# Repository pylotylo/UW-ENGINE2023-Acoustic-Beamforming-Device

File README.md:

# UW-ENGINE2023-Acoustic-Beamforming-Device
This is a repository for the UW ENGINE 2023 Acoustic Beamforming Device team. Here we can share drafts of our Kicad files, and any other code related to the project.

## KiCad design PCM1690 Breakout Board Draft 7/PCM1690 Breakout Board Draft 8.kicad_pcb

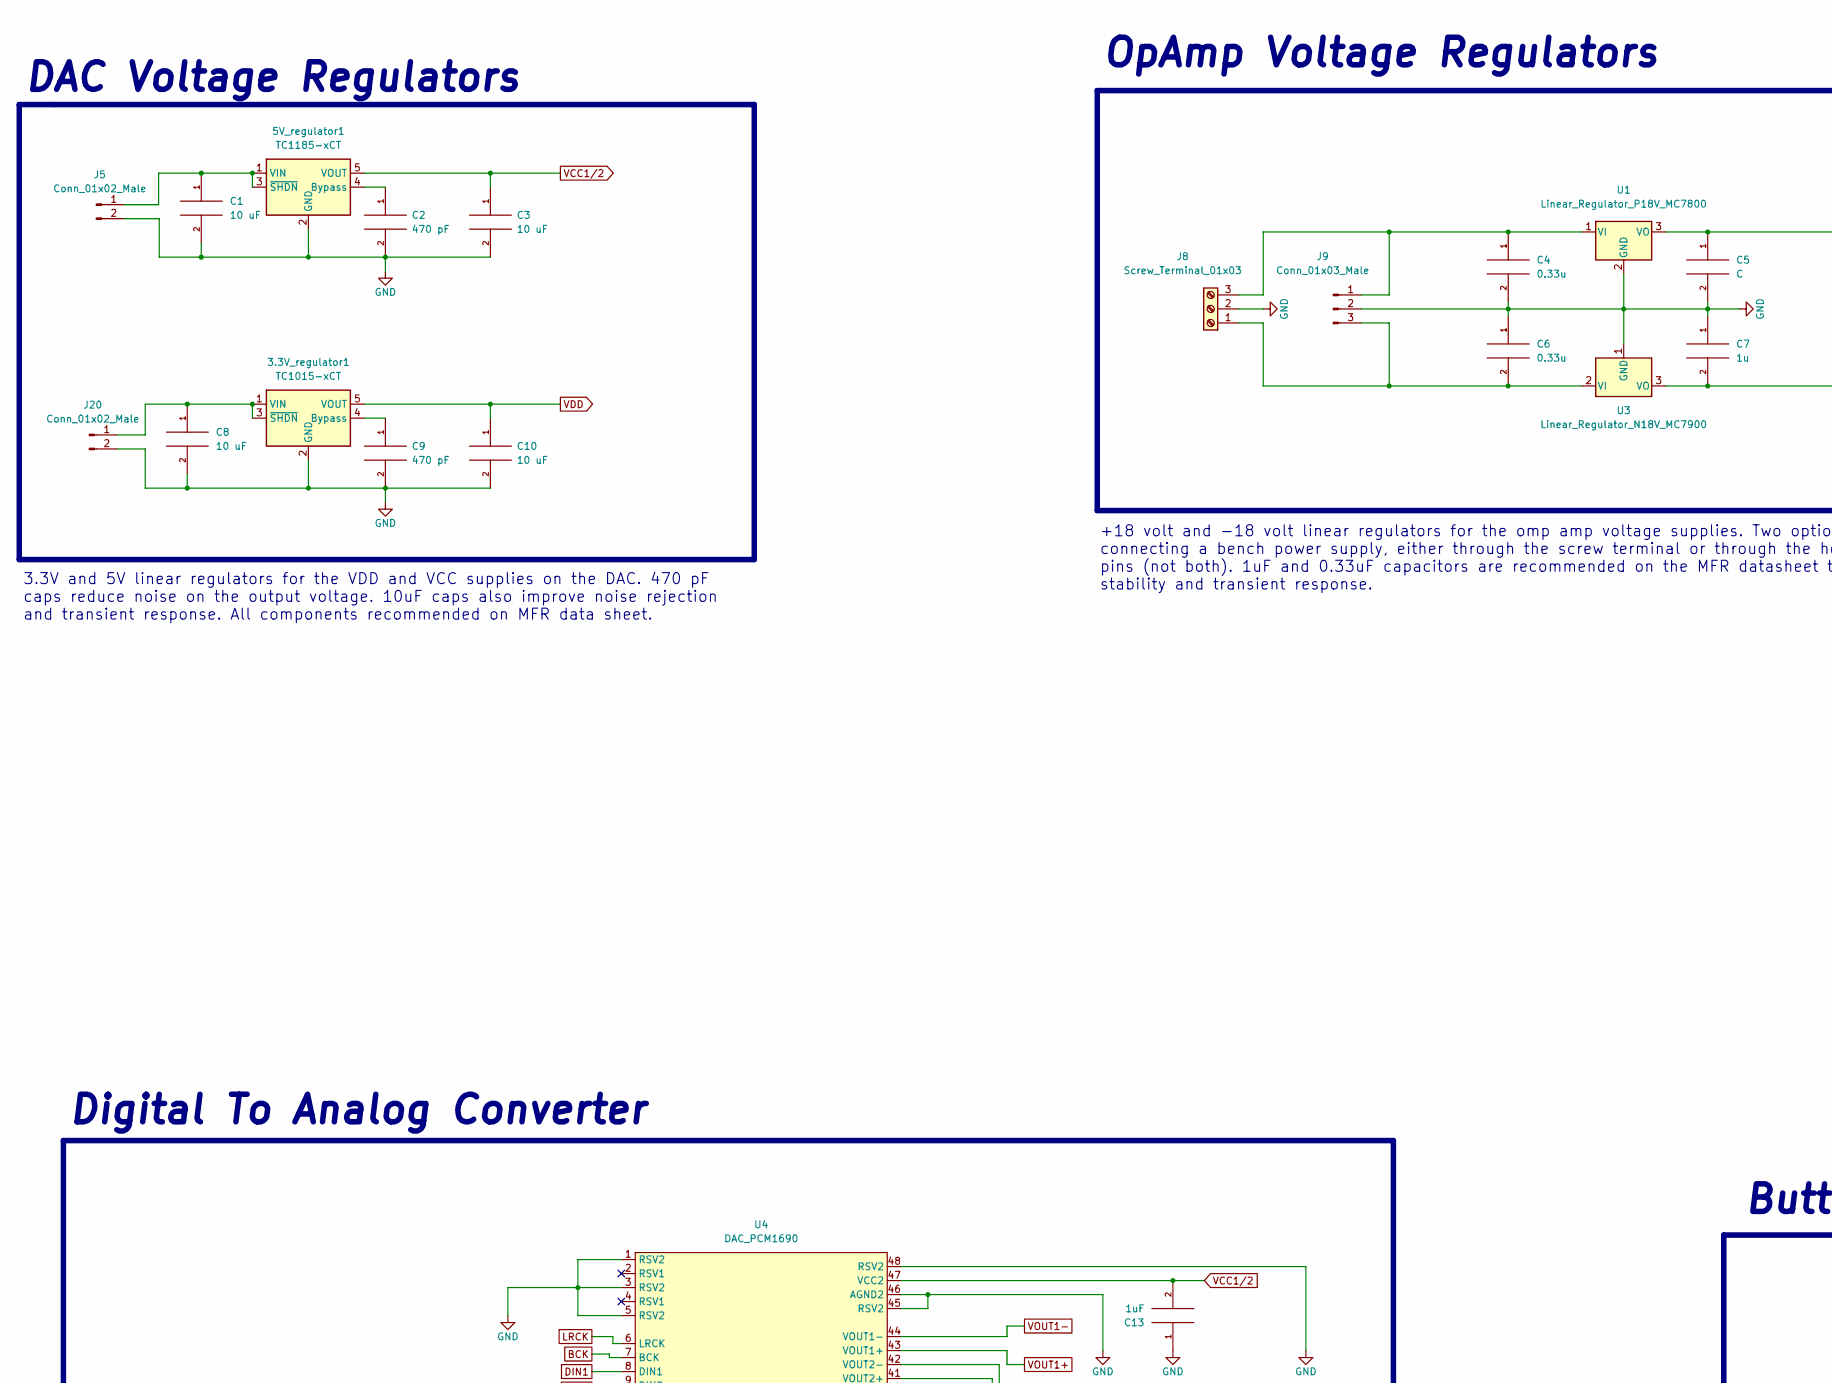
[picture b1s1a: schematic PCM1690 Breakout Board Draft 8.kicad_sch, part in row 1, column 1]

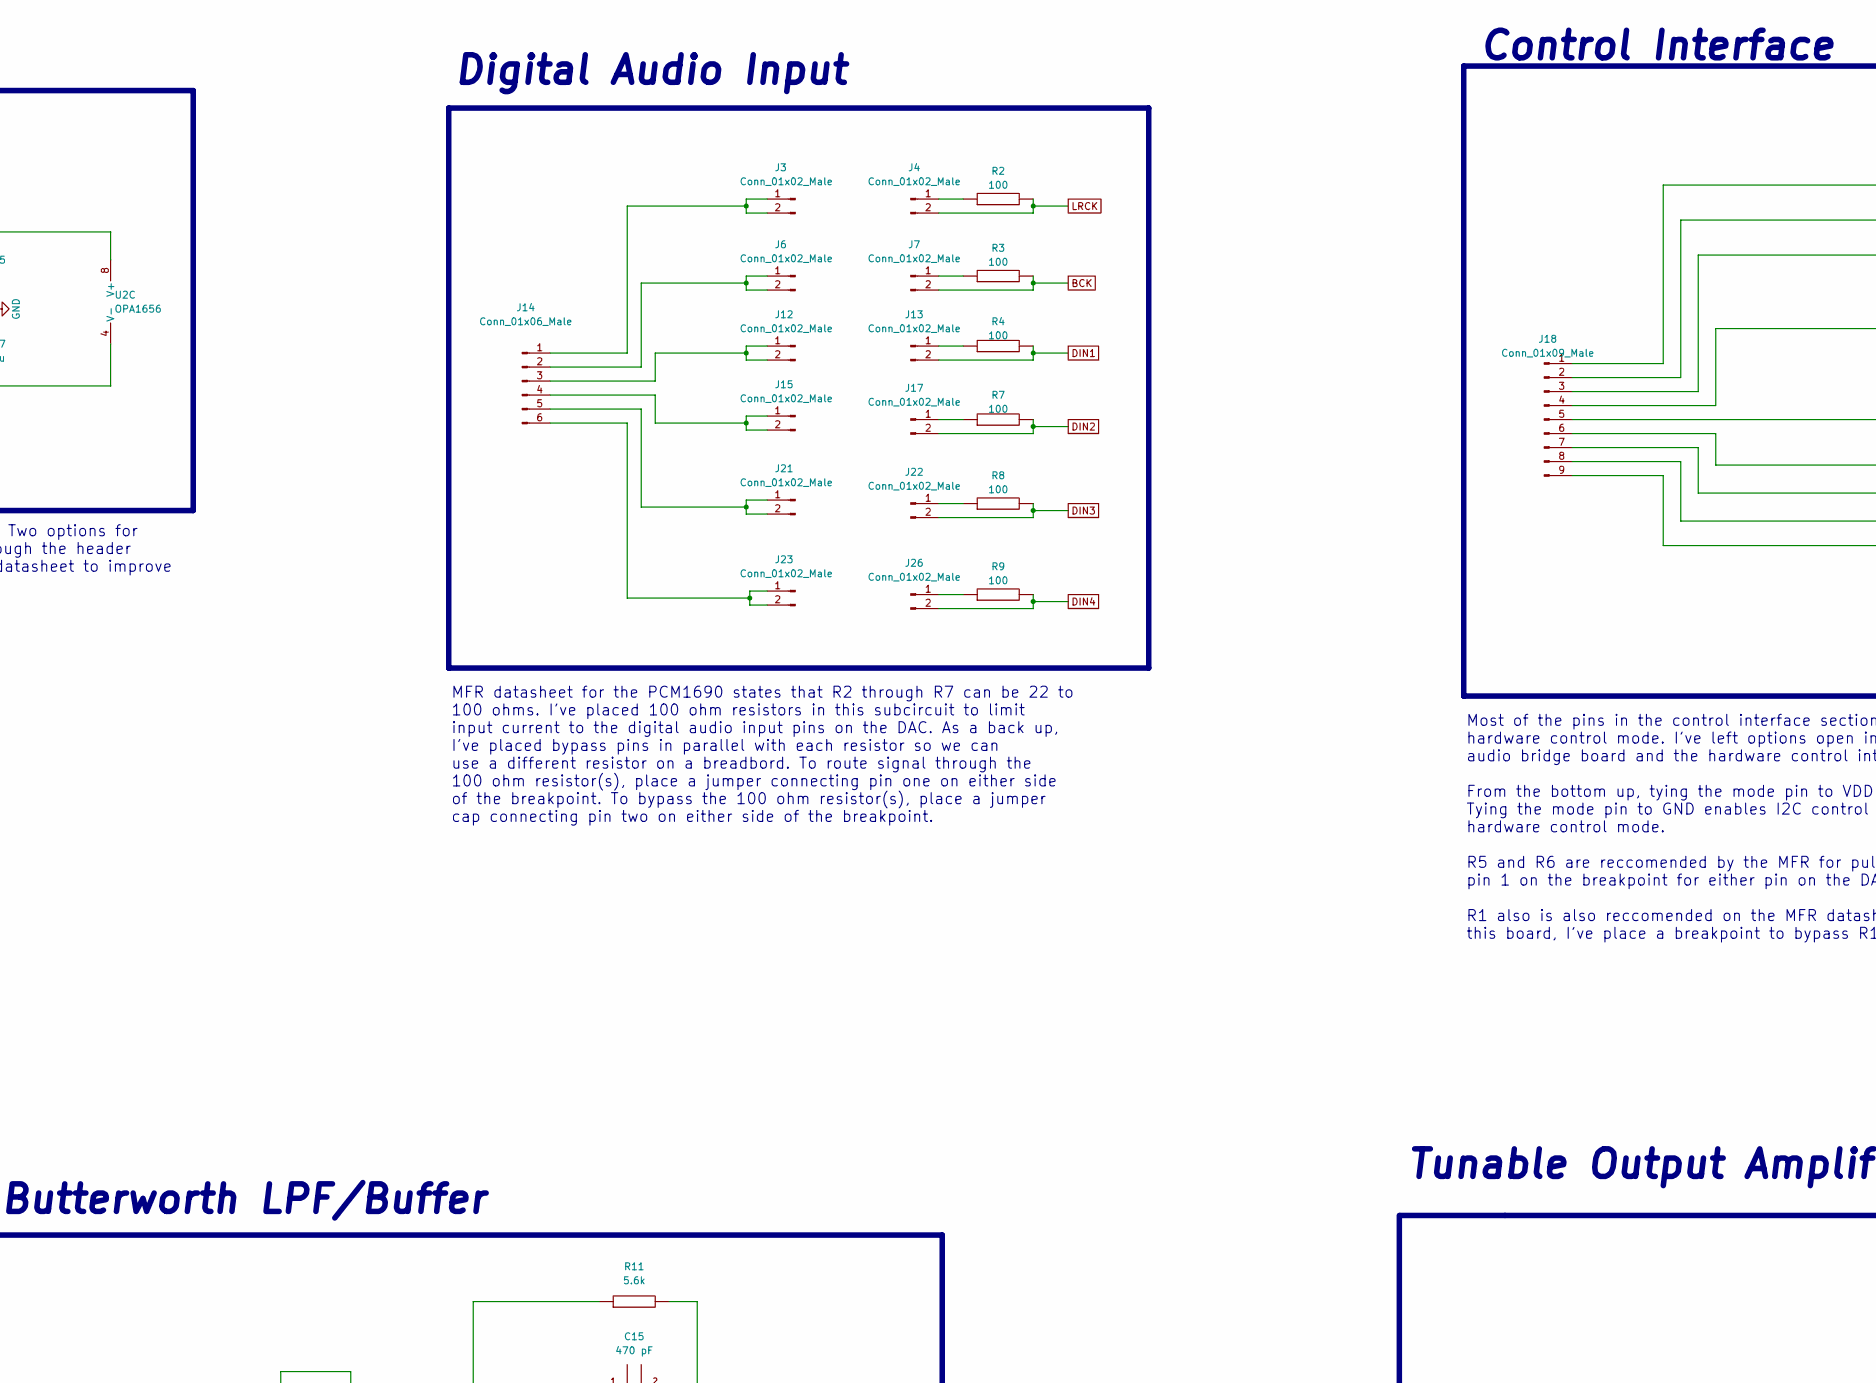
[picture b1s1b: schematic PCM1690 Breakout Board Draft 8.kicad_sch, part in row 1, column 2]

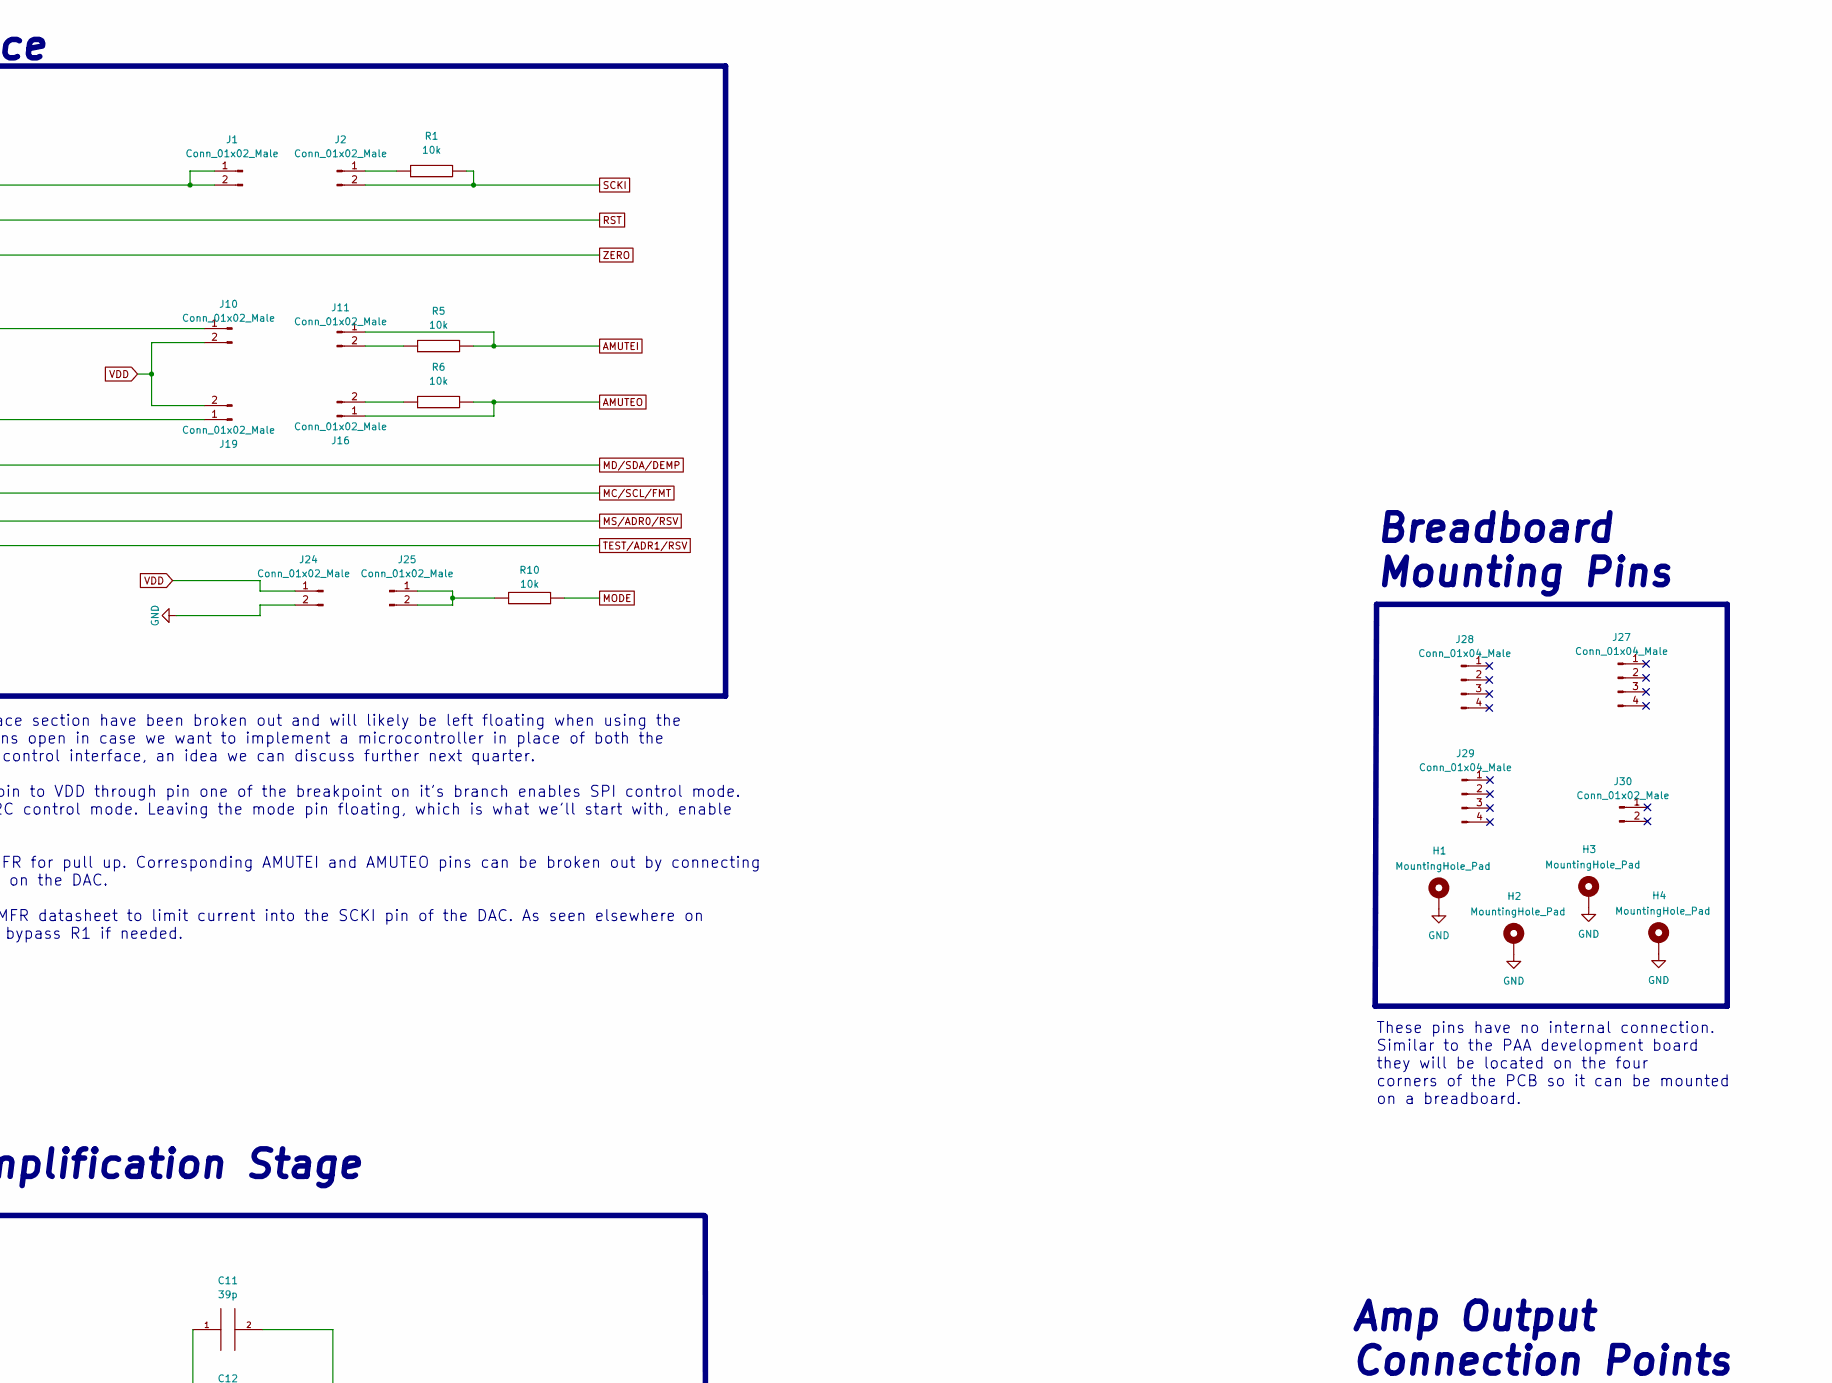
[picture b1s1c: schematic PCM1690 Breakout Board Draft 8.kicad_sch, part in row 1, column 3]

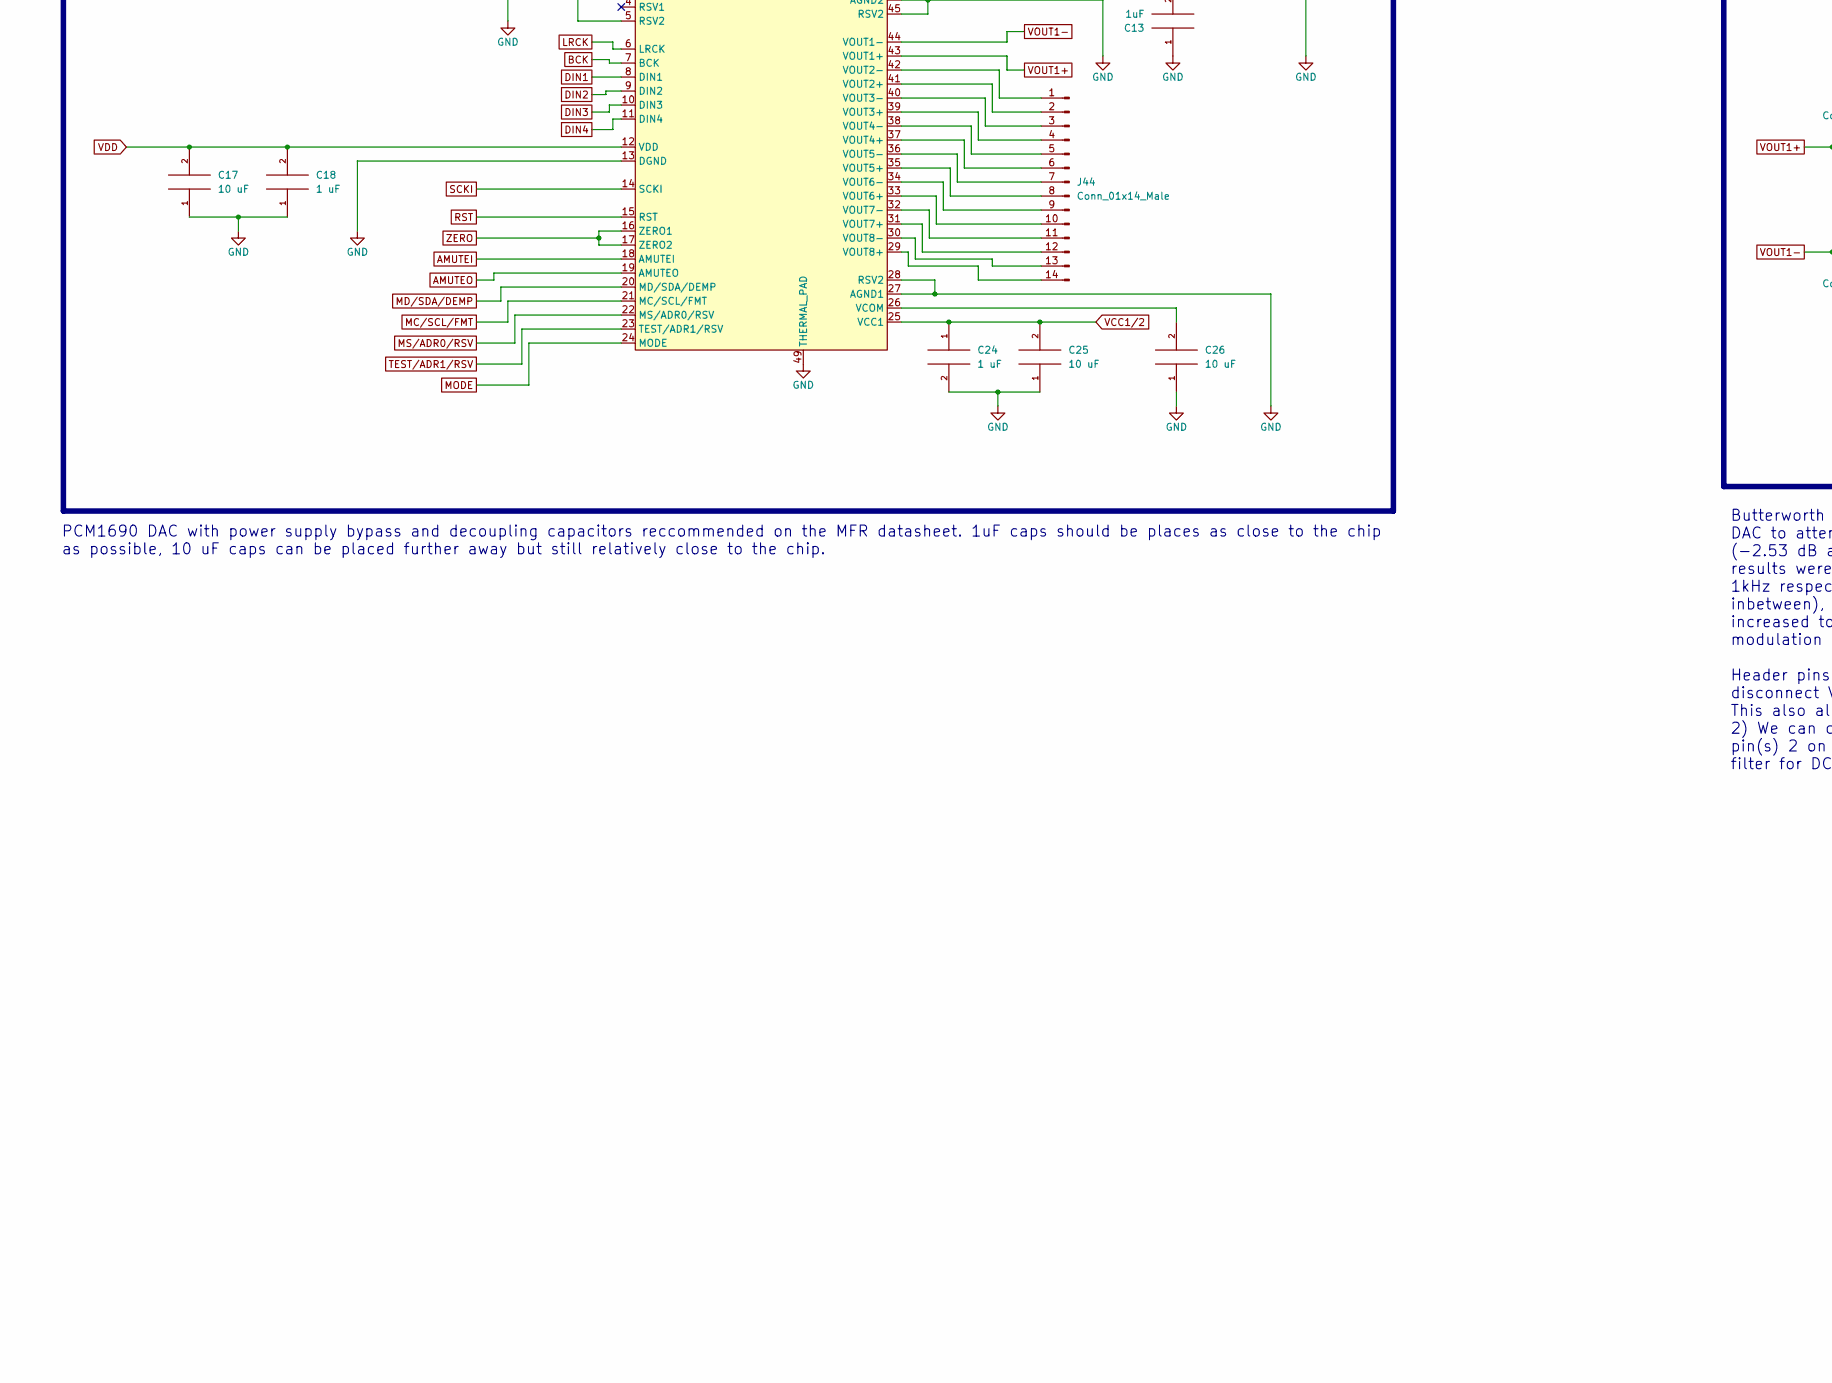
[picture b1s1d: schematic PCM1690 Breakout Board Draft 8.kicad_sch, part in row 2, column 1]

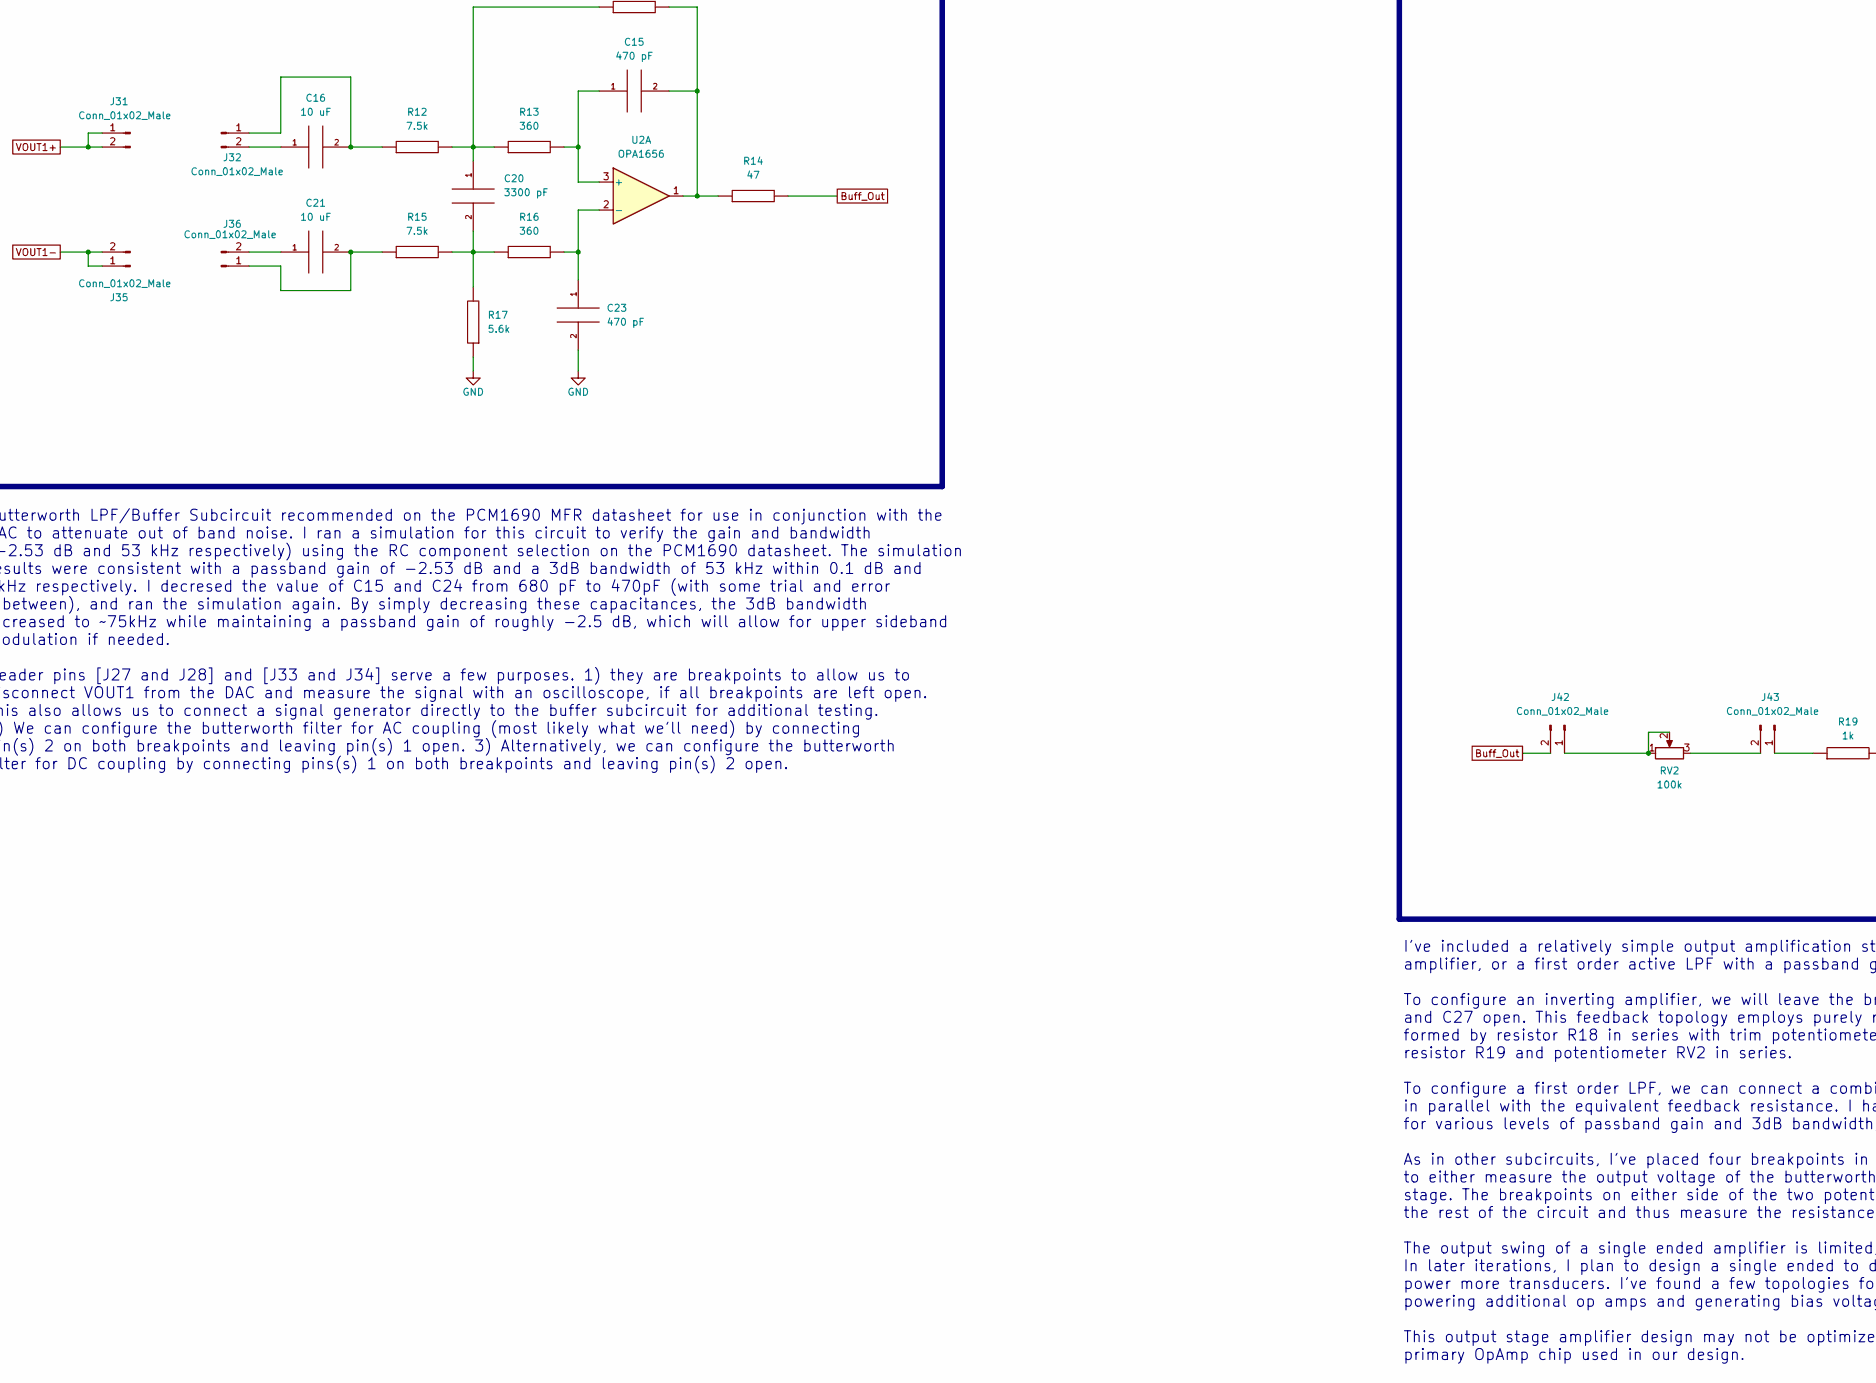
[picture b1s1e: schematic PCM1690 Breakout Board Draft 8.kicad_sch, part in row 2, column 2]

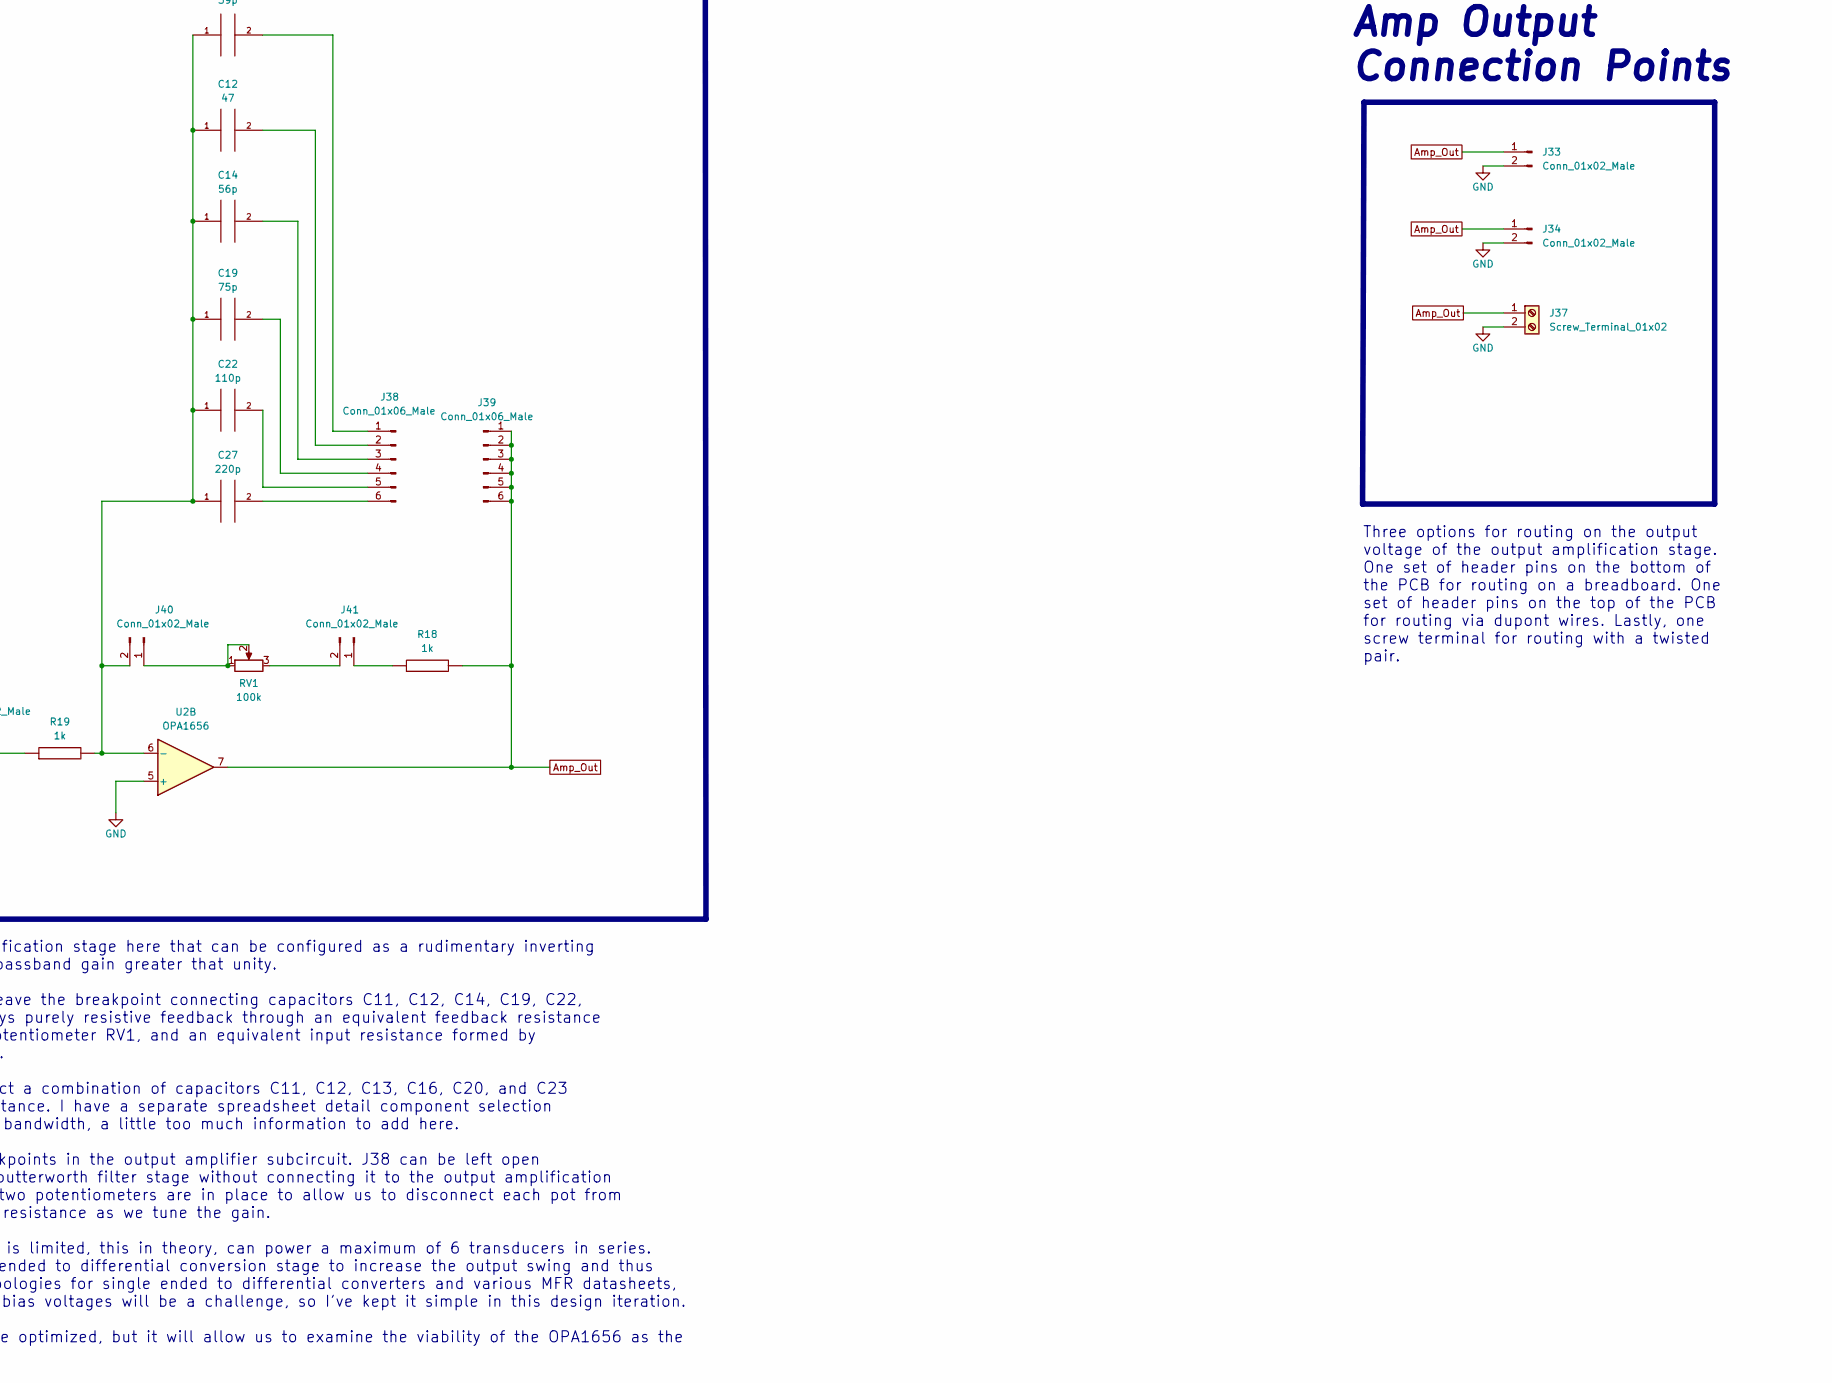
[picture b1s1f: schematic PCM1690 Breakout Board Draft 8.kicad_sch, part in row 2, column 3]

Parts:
3.3V_regulator1: TC1015-xCT; SOT-23-5
5V_regulator1: TC1185-xCT; SOT-23-5
C1, C3, C8, C10, C16, C17, C21, C25, C26: 10 uF; C_0603_1608Metric
C2, C9, C15, C23: 470 pF; C_0603_1608Metric
C4, C6: 0.33u; C_0603_1608Metric
C5: C; C_0603_1608Metric
C7: 1u; C_0603_1608Metric
C11: 39p; C_0603_1608Metric
C12: 47; C_0603_1608Metric
C13: 1uF; C_0603_1608Metric
C14: 56p; C_0603_1608Metric
C18, C24: 1 uF; C_0603_1608Metric
C19: 75p; C_0603_1608Metric
C20: 3300 pF; C_0603_1608Metric
C22: 110p; C_0603_1608Metric
C27: 220p; C_0603_1608Metric
H1, H2, H3, H4: MountingHole_Pad; MountingHole_4.3mm_M4_Pad_Via
J1, J2, J3, J4, J5, J6, J7, J10, J11, J12, J13, J15, J16, J17, J19, J20, J21, J22, J23, J24, J25, J26, J30, J31, J32, J33, J34, J35, J36, J40, J41, J42, J43: Conn_01x02_Male; PinHeader_1x02_P2.54mm_Vertical_NoCourtyard
J8: Screw_Terminal_01x03; TerminalBlock_bornier-3_P5.08mm
J9: Conn_01x03_Male; PinHeader_1x03_P2.54mm_Vertical_NoCourtyard
J14, J38, J39: Conn_01x06_Male; PinHeader_1x06_P2.54mm_Vertical_NoCourtyard
J18: Conn_01x09_Male; PinHeader_1x09_P2.54mm_Vertical_No_Courtyard
J27, J28, J29: Conn_01x04_Male; PinHeader_1x04_P2.54mm_Vertical_NoCourtyard
J37: Screw_Terminal_01x02; TerminalBlock_bornier-2_P5.08mm
J44: Conn_01x14_Male; PinHeader_1x14_P2.54mm_Vertical_NoCourtyard
R1, R5, R6, R10: 10k; R_0603_1608Metric_Pad0.98x0.95mm_HandSolder
R2, R3, R4, R7, R8, R9: 100; R_0603_1608Metric_Pad0.98x0.95mm_HandSolder
R11, R17: 5.6k; R_0603_1608Metric_Pad0.98x0.95mm_HandSolder
R12, R15: 7.5k; R_0603_1608Metric_Pad0.98x0.95mm_HandSolder
R13, R16: 360; R_0603_1608Metric_Pad0.98x0.95mm_HandSolder
R14: 47; R_0603_1608Metric_Pad0.98x0.95mm_HandSolder
R18, R19: 1k; R_0603_1608Metric_Pad0.98x0.95mm_HandSolder
RV1, RV2: 100k; Potentiometer_Bourns_3296W_Vertical
U1: Linear_Regulator_P18V_MC7800; TO-220-3_Vertical
U2: OPA1656; OPA1656_SOIC-8_3.9x5.4mm_P1.27mm
U3: Linear_Regulator_N18V_MC7900; TO-220-3_Vertical
U4: DAC_PCM1690; PCM1690_No_Courtyard_Thermal

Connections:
AMUTEI: J11.1, R5.2, U4.18 (AMUTEI)
AMUTEO: J16.1, R6.2, U4.19 (AMUTEO)
Amp_Out: J33.1, J34.1, J37.1, J39.1, J39.2, J39.3, J39.4, J39.5, J39.6, R18.2, U2.7
BCK: J7.2, R3.2, U4.7 (BCK)
Buff_Out: J42.2, R14.2
DIN1: J13.2, R4.2, U4.8 (DIN1)
DIN2: J17.2, R7.2, U4.9 (DIN2)
DIN3: J22.2, R8.2, U4.10 (DIN3)
DIN4: J26.2, R9.2, U4.11 (DIN4)
GND: 3.3V_regulator1.2 (GND), 5V_regulator1.2 (GND), C1.2, C2.2, C3.2, C4.2, C5.2, C6.1, C7.1, C8.2, C9.2, C10.2, C13.1, C17.1, C18.1, C23.2, C24.2, C25.1, C26.1, H1.1, H2.1, H3.1, H4.1, J5.2, J8.2, J9.2, J20.2, J24.2, J33.2, J34.2, J37.2, R17.1, U1.2 (GND), U2.5 (+), U3.1 (GND), U4.1 (RSV2), U4.3 (RSV2), U4.5 (RSV2), U4.13 (DGND), U4.27 (AGND1), U4.28 (RSV2), U4.45 (RSV2), U4.46 (AGND2), U4.48 (RSV2), U4.49 (THERMAL_PAD)
LRCK: J4.2, R2.2, U4.6 (LRCK)
MC/SCL/FMT: J18.7, U4.21 (MC/SCL/FMT)
MD/SDA/DEMP: J18.6, U4.20 (MD/SDA/DEMP)
MODE: R10.1, U4.24 (MODE)
MS/ADR0/RSV: J18.8, U4.22 (MS/ADR0/RSV)
unnamed: 3.3V_regulator1.1 (VIN), 3.3V_regulator1.3 (~SHDN), C8.1, J20.1
unnamed: 3.3V_regulator1.4 (Bypass), C9.1
unnamed: 5V_regulator1.1 (VIN), 5V_regulator1.3 (~SHDN), C1.1, J5.1
unnamed: 5V_regulator1.4 (Bypass), C2.1
unnamed: C4.1, J8.3, J9.1, U1.1 (VI)
unnamed: C5.1, U1.3 (VO), U2.8 (V+)
unnamed: C6.2, J8.1, J9.3, U3.2 (VI)
unnamed: C7.2, U2.4 (V-), U3.3 (VO)
unnamed: C11.1, C12.1, C14.1, C19.1, C22.1, C27.1, J40.2, R19.2, U2.6 (-)
unnamed: C11.2, J38.1
unnamed: C12.2, J38.2
unnamed: C14.2, J38.3
unnamed: C15.1, R13.2, U2.3 (+)
unnamed: C15.2, R11.2, R14.1, U2.1
unnamed: C16.1, J32.2
unnamed: C16.2, J32.1, R12.1
unnamed: C19.2, J38.4
unnamed: C20.1, R11.1, R12.2, R13.1
unnamed: C20.2, R15.2, R16.1, R17.2
unnamed: C21.1, J36.2
unnamed: C21.2, J36.1, R15.1
unnamed: C22.2, J38.5
unnamed: C23.1, R16.2, U2.2 (-)
unnamed: C26.2, U4.26 (VCOM)
unnamed: C27.2, J38.6
unnamed: J1.1, J1.2, J18.1
unnamed: J2.1, R1.1
unnamed: J4.1, R2.1
unnamed: J7.1, R3.1
unnamed: J10.1, J18.4
unnamed: J11.2, R5.1
unnamed: J12.1, J12.2, J14.3
unnamed: J13.1, R4.1
unnamed: J3.1, J3.2, J14.1
unnamed: J6.1, J6.2, J14.2
unnamed: J14.4, J15.1, J15.2
unnamed: J14.5, J21.1, J21.2
unnamed: J14.6, J23.1, J23.2
unnamed: J16.2, R6.1
unnamed: J17.1, R7.1
unnamed: J18.5, J19.1
unnamed: J22.1, R8.1
unnamed: J25.1, J25.2, R10.2
unnamed: J26.1, R9.1
unnamed: J40.1, RV1.1, RV1.2
unnamed: J41.1, R18.1
unnamed: J41.2, RV1.3
unnamed: J42.1, RV2.1, RV2.2
unnamed: J43.1, R19.1
unnamed: J43.2, RV2.3
unnamed: J44.1, U4.42 (VOUT2-)
unnamed: J44.2, U4.41 (VOUT2+)
unnamed: J44.3, U4.40 (VOUT3-)
unnamed: J44.4, U4.39 (VOUT3+)
unnamed: J44.5, U4.38 (VOUT4-)
unnamed: J44.6, U4.37 (VOUT4+)
unnamed: J44.7, U4.36 (VOUT5-)
unnamed: J44.8, U4.35 (VOUT5+)
unnamed: J44.9, U4.34 (VOUT6-)
unnamed: J44.10, U4.33 (VOUT6+)
unnamed: J44.11, U4.32 (VOUT7-)
unnamed: J44.12, U4.31 (VOUT7+)
unnamed: J44.13, U4.30 (VOUT8-)
unnamed: J44.14, U4.29 (VOUT8+)
RST: J18.2, U4.15 (RST)
SCKI: J2.2, R1.2, U4.14 (SCKI)
TEST/ADR1/RSV: J18.9, U4.23 (TEST/ADR1/RSV)
VCC1/2: 5V_regulator1.5 (VOUT), C3.1, C13.2, C24.1, C25.2, U4.25 (VCC1), U4.47 (VCC2)
VDD: 3.3V_regulator1.5 (VOUT), C10.1, C17.2, C18.2, J10.2, J19.2, J24.1, U4.12 (VDD)
VOUT1+: J31.1, J31.2, U4.43 (VOUT1+)
VOUT1-: J35.1, J35.2, U4.44 (VOUT1-)
ZERO: J18.3, U4.16 (ZERO1), U4.17 (ZERO2)

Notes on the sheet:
PCM1690 DAC with power supply bypass and decoupling capacitors reccommended on the MFR datasheet. 1uF caps should be places as close to the chip as possible, 10 uF caps can be placed further away but still relatively close to the chip.
Butterworth LPF/Buffer
MFR datasheet for the PCM1690 states that R2 through R7 can be 22 to 100 ohms. I've placed 100 ohm resistors in this subcircuit to limit input current to the digital audio input pins on the DAC. As a back up, I've placed bypass pins in parallel with each resistor so we can use a different resistor 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
Tunable Output Amplification Stage
DAC Voltage Regulators
OpAmp Voltage Regulators
Digital Audio Input
I've included a relatively simple output amplification stage here that can be configured as a rudimentary inverting amplifier, or a first order active LPF with a passband gain greater that unity. To configure an inverting amplifier, we will leave the breakpoint connecting capacitors C11, C12, C14, 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
Breadboard Mounting Pins
Most of the pins in the control interface section have been broken out and will likely be left floating when using the hardware control mode. I've left options open in case we want to implement a microcontroller in place of both the audio bridge board and the hardware control interface, an idea we 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
3.3V and 5V linear regulators for the VDD and VCC supplies on the DAC. 470 pF caps reduce noise on the output voltage. 10uF caps also improve noise rejection and transient response. All components recommended on MFR data sheet.
Digital To Analog Converter
These pins have no internal connection. Similar to the PAA development board they will be located on the four corners of the PCB so it can be mounted on a breadboard.
Amp Output Connection Points
Control Interface
Three options for routing on the output voltage of the output amplification stage. One set of header pins on the bottom of the PCB for routing on a breadboard. One set of header pins on the top of the PCB for routing via dupont wires. Lastly, one screw terminal for routing with a twisted pair.
Butterworth LPF/Buffer Subcircuit recommended on the PCM1690 MFR datasheet for use in conjunction with the DAC to attenuate out of band noise. I ran a simulation for this circuit to verify the gain and bandwidth (-2.53 dB and 53 kHz respectively) using the RC component selection on the PCM1690 data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
+18 volt and -18 volt linear regulators for the omp amp voltage supplies. Two options for connecting a bench power supply, either through the screw terminal or through the header pins (not both). 1uF and 0.33uF capacitors are recommended on the MFR datasheet to improve stability and transient respo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

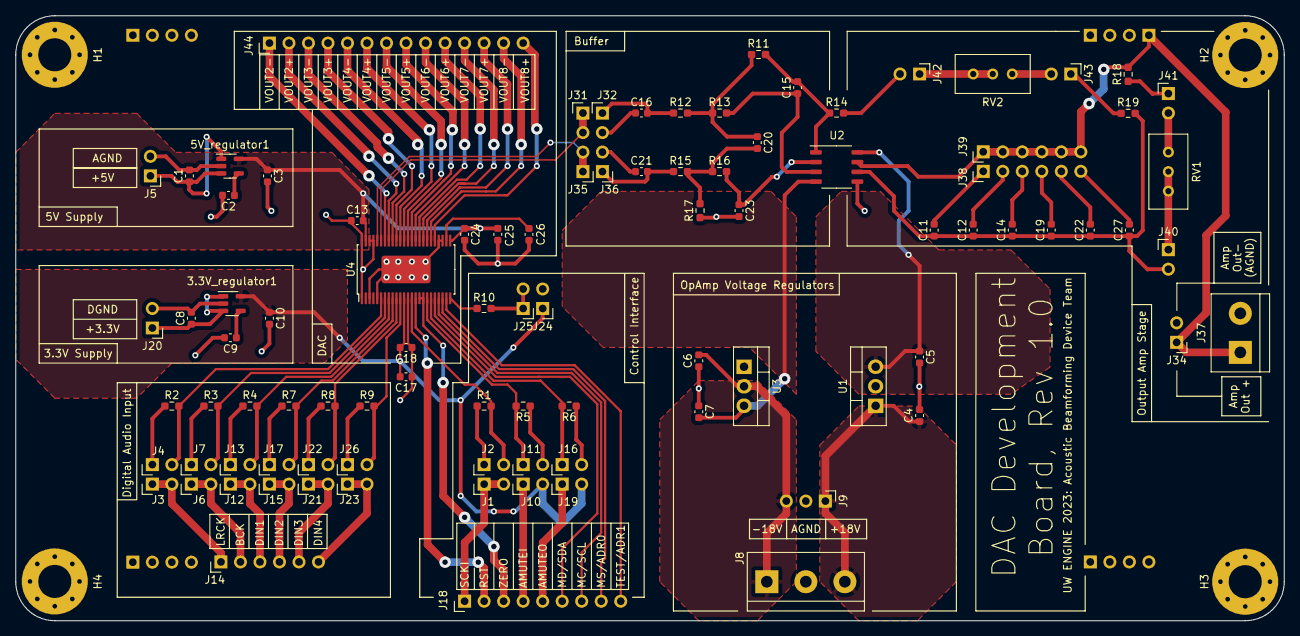
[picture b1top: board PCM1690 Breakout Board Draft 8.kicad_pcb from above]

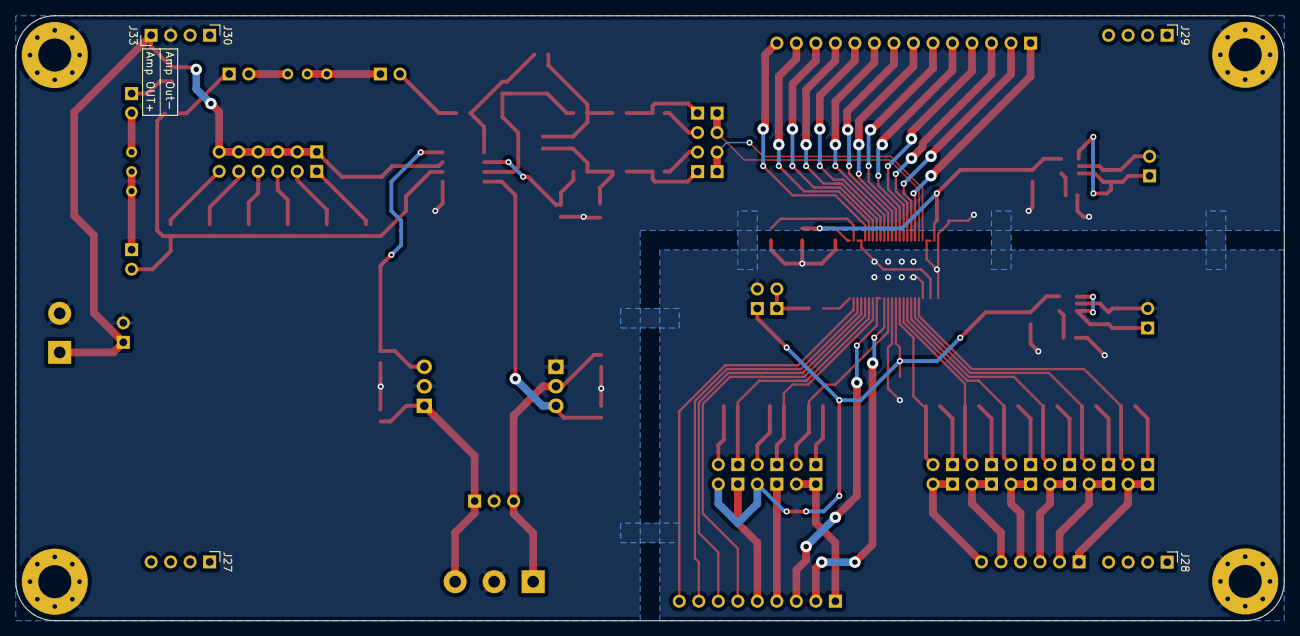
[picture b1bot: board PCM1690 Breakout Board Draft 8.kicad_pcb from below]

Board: 2 copper layers, 165.1 x 78.7 mm, 102 parts (5 on the bottom side), 87 nets.
